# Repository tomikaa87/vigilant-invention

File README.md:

# vigilant-invention
This is just my playground repository where I store various hobby projects 

# ShutterMotorController
A simple IoT controller for electronic window shutter belt winders.

# ESPControlCenter
An attempt to make a small home automation control center with ESP8266.

# ChargeController
A smart plug build with an ESP8266 WiFi controller and a companion application for Android to turn on/off charging the phone automatically when the battery charge level reaches the given thresholds.

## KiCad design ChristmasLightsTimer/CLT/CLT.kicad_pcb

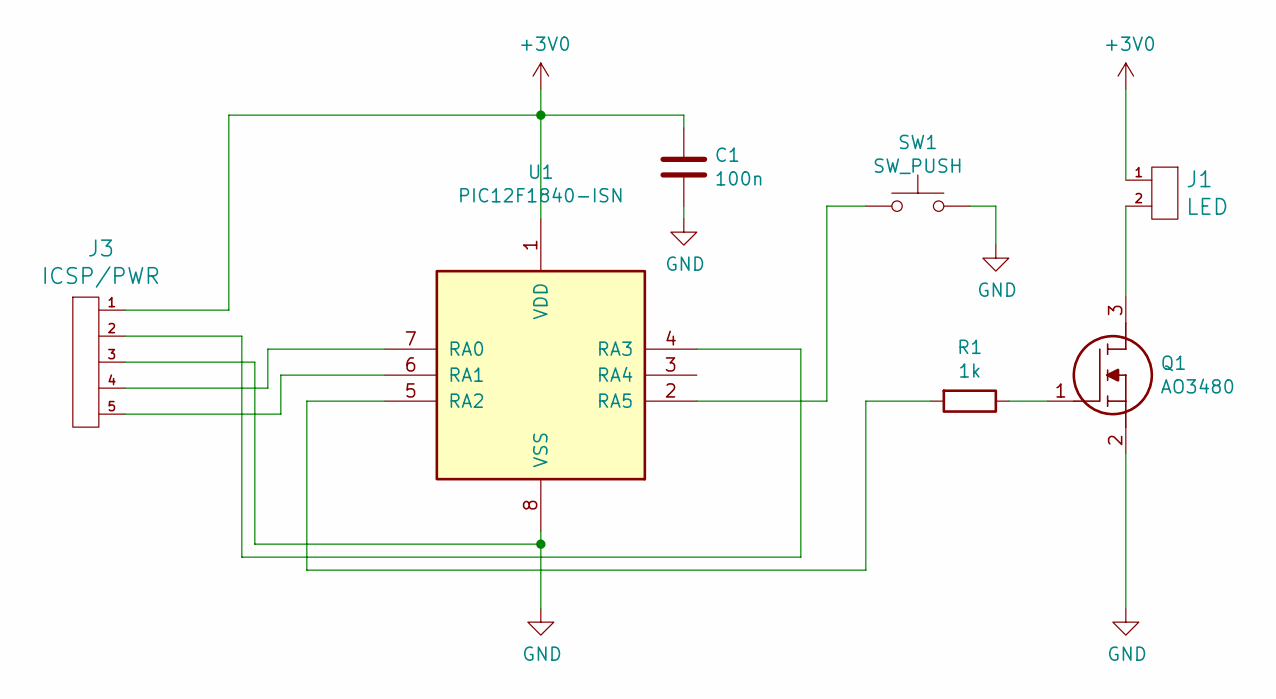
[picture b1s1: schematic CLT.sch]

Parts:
C1: 100n; C_0805_2012Metric_Pad1.15x1.40mm_HandSolder
J1: LED; PinHeader_1x02_P2.54mm_Vertical
J3: ICSP/PWR; PinHeader_2x03_P2.54mm_Vertical
Q1: AO3480; SOT95P280X125-3N; Manufacturer_Part_Number AO3480
R1: 1k; R_0805_2012Metric_Pad1.15x1.40mm_HandSolder
SW1: SW_PUSH; SW_Push_1P1T_NO_6x6mm_FSM2JSMA
U1: PIC12F1840-ISN; SOIC-8_3.9x4.9mm_P1.27mm

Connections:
+3V0: C1.1, J1.1, J3.1, U1.1 (VDD)
GND: C1.2, J3.3, Q1.2, SW1.2, U1.8 (VSS)
unnamed: J1.2, Q1.3
unnamed: J3.2, U1.4 (RA3)
unnamed: J3.4, U1.7 (RA0)
unnamed: J3.5, U1.6 (RA1)
unnamed: Q1.1, R1.1
unnamed: R1.2, U1.5 (RA2)
unnamed: SW1.1, U1.2 (RA5)

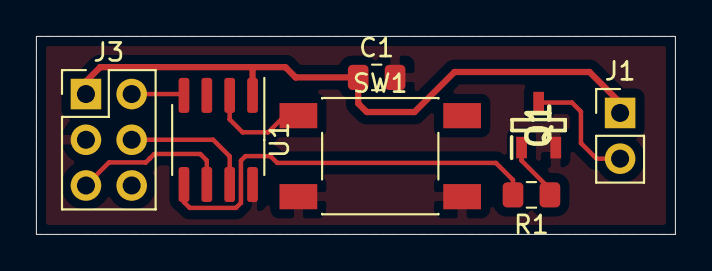
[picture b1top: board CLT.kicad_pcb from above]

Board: 2 copper layers, 35.5 x 11.0 mm, 7 parts (0 on the bottom side), 9 nets.

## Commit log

2018-01-08 Add ESPControlCenter
2018-01-29 Add ShutterMotorController
2018-01-29 SMC: fix screw terminal pin pitch; route +3.3V to DS18B20 differently
2018-02-03 ESPControlCenter: add RPi playground project
2018-02-03 ESPControlCenter playground: move sources to src
2018-02-03 ESPControlCenter: add more characters to PxPlus VGA8 32px; update playground
2018-02-03 ESPControlCenter: add crypto, drivers, ui
2018-02-03 Update gitignore
2018-02-03 ESPControlCenter: add NAS status screen to Playground
2018-02-03 ESPControlCenter-Playground: move screens to a separate folder
2018-02-03 ESPControlCenter-Playground: initial commit of air conditioner screen
2018-02-03 ESPControlCenter-Playground: implement AC fan speed indicator
2018-02-11 SMC: add indicator LED
2018-02-11 SMC: initial commit of the Firmware
2018-02-12 SMC: initial commit of BlynkHandler and RelayController
2018-02-12 SMC: handle Blynk button presses
2018-02-12 SMC: add ADC header to the PCB
2018-02-13 SMC: implement relay grouping in RelayController
2018-02-13 SMC: do some cosmetic changes
2018-02-13 SMC: add Clock module with NTP support
2018-02-16 SMC: fix DRC errors of board design
2018-02-18 SMC: fix screw-terminal pin pitch and drawing
2018-02-18 SMC: increase clearance between switched relay tracks
2018-02-18 SMC: increase annular ring size of screw terminals
2018-02-20 SMC: use const-correct version of NTPClient
2018-02-25 SMC: implement persistent config and automation timer
2018-02-28 SMC: implement a more clever logging mechanism
2018-02-28 SMC: fix logger prefixes; add some more logging; don't log to Blynk while it's disconnected
2018-02-28 SMC: create README.md
2018-03-18 Add Eagle libraries used by the sub-projects
2018-03-18 ShutterMotorRemoteReceiver: initial commit
2018-06-26 SMCH: add stm32f4discovery prototype project
2018-06-26 SMCH: move prototype project to a separate folder
2018-06-26 SMCH: add SMRHubTest prototype project
2018-06-26 SMRR: add STM32F103 (MX) prototype project
2018-06-26 SMCH: update SMRHubTest
2018-06-26 SMCH: disable USB host code, move lwIP buffers to CCMRAM
2018-06-27 SMCH: convert proto to a C++ project
2018-06-27 SMCH: format and clean-up proto code
2018-06-27 SMCH: initial commit of proto TestSocket
2018-06-30 SMCH: implement basic TCP communication in the proto
2018-07-01 SMCH: initial commit of Blynk in proto
2018-07-03 SMCH: initial commit of a very basic Qt implementation
2018-08-04 Shutter Motor Remote Receiver: inital commit
2018-08-18 SMC: fix DST handling
2018-08-18 SMRR: reset PLOS_CNT when it reaches 15
2018-08-19 SMCH: reset PLOS_CNT when it reaches 15
2018-08-19 SMCH: reset PLOS_CNT on mode switch; clean up the code
2018-08-19 SMRR: reset PLOS_CNT on switching mode
2018-08-19 SMCH: show "scan" and "read status" output on Diag Terminal
2018-08-20 SMCH: initial commit of new interfaces
2018-08-21 SMCH: initial commit of new Hub implementation
2018-09-13 SMRR: increase RF output power to 0 dbm
2018-09-13 SMCH: attempt to avoid stuck state
2018-09-19 SMCH: fix compilation errors with non-MSVC compilers
2018-09-24 SMCH: add kitchen shutters, use step up/down widgets instead of buttons
2018-09-24 SMCH: enable debugging, fix nrf24_dump_registers
2018-10-13 Scheduling with Blynk
2018-10-13 SMCH: move files around
2018-10-13 Add Qt shadow build directories to gitignore
2018-10-13 SMCH: move git submodules under 3rdparty
2018-10-13 SMCH: fix include paths
2018-10-13 SMCH: initial commit of the future-based interface
2018-10-13 SMCH: implement logging helpers, clean up the code
2018-10-14 SMCH: implement basic hub functions with OperationQueue
2018-10-14 SMCH: clean up the code a little bit
2018-10-14 SMCH: fix device creation during scan
2018-10-16 SMCH: initial commit of new Radio
2018-10-16 SMCH: implement (almost) working Radio
2018-10-16 SMCH: add Radio implementation
2018-10-16 SMRR: implement delay before sending the response to the Hub
2018-10-16 SMRR: add extra clean up code to mode switching logic
2018-10-16 SMRR: implement ALL UP and ALL DOWN commands
2018-10-16 SMCH: tweak Radio a little bit
2018-11-10 SMCH: initial commit of new Diag Menu; enable C++17
2018-11-10 SMCH: clean up, optimizations
2018-11-10 SMCH: add device status query to Hub
2018-11-10 SMCH: implement some device functions in Diag Menu
2018-11-10 SMRR: initial commit of OpenBLT-based bootloader
2018-11-10 SMRR-BL: enable multiprocessor compilation, disable USART
2018-11-10 SMRR-BL: increase reserved flash size
2018-11-10 SMRR: reserve flash space for the bootloader
2018-11-11 SMCH: implement more detailed device info
2018-12-15 Add ChristmastLightsTimer
2018-12-15 Initial commit of ChargeController
2018-12-18 New ChargeController schematics for proto board
2018-12-31 Initial commit of TouchScreenTest
2018-12-31 TouchScreenTest: clean up TPFilter
2018-12-31 TouchScreenTest: fix the project
2018-12-31 TouchScreenTest: clean up the code
2018-12-31 TouchScreenTest: remove factory test images
2019-01-01 TouchScreenTest: implement proper 8080 parallel control; implement SetPixel via RMW
2019-01-02 TouchScreenTest: implement multi color drawing test
2019-01-05 TouchScreenTest: initial commit of simple widget support
2019-01-06 ChargeController: initial commit of Android app
2019-01-06 ChargeController: add new launcher icon
2019-01-10 TouchScreenTest: use multi channel ADC with DMA to handle the touchpad
2019-01-10 TouchScreenTest: adjust touchpad detect threshold; fix Rect
2019-01-19 ChargeController: initial commit of notification update
2019-01-19 ChargerController: migrate to AndroidX
2019-01-19 ChargeController: improve notification
2019-01-19 ChargeController: initial commit of Firmware
2019-01-19 ChargeController: update Android project
2019-01-19 ChargeController: implement power output keep-alive
2019-01-19 ChargeController: add script which starts serial monitor
2019-01-19 ChargeController: update output state on the notification properly
2019-01-19 ChargeController: notification alerts only once
2019-01-19 Update README.md
    Add ChargeController
2019-01-26 ChargeController: implement smarter LED control in the firmware
2019-01-26 ChargerController: increase keep-alive interval
2019-01-26 ChargeController: disable AP mode in ESP
2019-01-27 ChargeController: simplify the Timer
2019-01-27 ChargeController: clean-up the firmware code
2019-01-30 ShutterMotorController: use local blynk server
2019-01-30 ChargeController: greatly improve connection stability
2019-01-31 ChargeController: disable backup to avoid killing the service
2019-04-17 ChargeController: replace hardwired charging limits
2019-04-17 ChargeController: add logging
2019-04-17 ChargeController: update gradle
2019-04-18 ChargeController: re-enable output in keep-alive task after the connection is restored
2019-05-03 TeveclubAutomator: initial commit
2019-05-03 TeveclubAutomator: update QMake project
2019-05-04 TeveclubAutomator: initial commint of main page handler
2019-05-04 TeveclubAutomator: implement feeding
2019-05-04 TeveclubAutomator: implement teaching
2019-05-05 TeveclubAutomator: prepare to be used with Cron
2019-05-05 TeveclubAutomator: fix QMake project for Linux
2019-05-05 TeveclubAutomator: add check for login result
2019-05-14 TeveclubAutomator: fix stuck state when only one action is selected, rename configuration file
2019-05-14 ChargeController: use domain name instead of fix IP
2019-05-14 TeveclubAutomator: implement random skill selection from teaching page
2019-05-14 TeveclubAutomator: fix spelling error on the help screen
2019-05-15 TeveclubAutomator: implement smarter state/action handling
2019-05-15 TeveclubAutomator: implement proper teaching form handling
2019-05-15 TeveclubAutomator: implement playing with the Wonderful One Number game
2019-08-16 ChristmasLightsTimer: implement ON period setting
2019-08-17 ChristmasLightsTimer: improve button handling, clean-up the code
2019-08-17 ChristmasLightsTimer: optimize the code
2019-08-17 ChristmasLightsTimer: clarify the code a little bit
2019-08-17 ChristmasLightsTimer: fix minor issues
2019-12-31 Add FlowerGuard flower watering alarm
2020-11-07 SMRR: add test project for ST32F103
2021-09-02 CLT: implementation for 12F1840, add tuning options to 12F683
2021-09-02 CLT: add schematics and PCB design with 12F1840
2022-01-13 Add pico-snowfall
2022-01-13 Add pico-oled-widgets
2022-01-13 Add pico-bufferless-oled
2022-01-14 Add ChristmasLightsTimer v2
2022-01-15 pico-oled-widgets: fix text drawing
2022-01-15 pico-oled-widgets: implement simple text clipping
2022-11-26 pico-snowfall: add battery voltage measurement
2023-01-08 pic-snowfall: initial commit
2023-01-08 pic-snowfall: reduce memory usage of snow pile heights structure
2023-01-08 pic-snowfall: clean up the code
2023-01-08 pic-snowfall: prepare the code for the buffer-less implementation
2023-01-08 pic-snowfall: implement bufferless drawing (very slow at the moment)
2023-01-08 pic-snowfall: optimize a bit
2023-01-09 pic-snowfall: optimize speed of bufferless drawing
